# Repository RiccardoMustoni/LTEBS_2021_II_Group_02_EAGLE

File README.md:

# LTEBS_2021_II_Group_02_EAGLE

### Final Version 
The aim of the project is to design a PCB embedding the PSoC 5LP micro-controller in order to evaluate its performance and to determine if such uC is suitable for the project. The PCB embeds the CY8CKIT-059 kit, which will be soldered on male jumpers, and other additional components required to coduct the proper testing. 

The project consists in the design of a schematic, a board, and a library containing the necessary components. Design rules are added according to the technical specifications reported in the manufacturer website MDSrl.

### Project Folder 
The folder contains the schematic ("Group_02.sch") and the board ("Group_02.brd") used to create the final PCB.

### Library Folder 
The folder contains the library ("Group_02_Library.lbr") for the components TCA9546A and TMUX1208 with footprints, symbols and devices. 

### Design Rules Folder 
The folder contains the design rules ("Group_02.dru") according to the technical info on the manufacturer website. 

### Contributors 

Mancini Giorgia,
Mustoni Riccardo

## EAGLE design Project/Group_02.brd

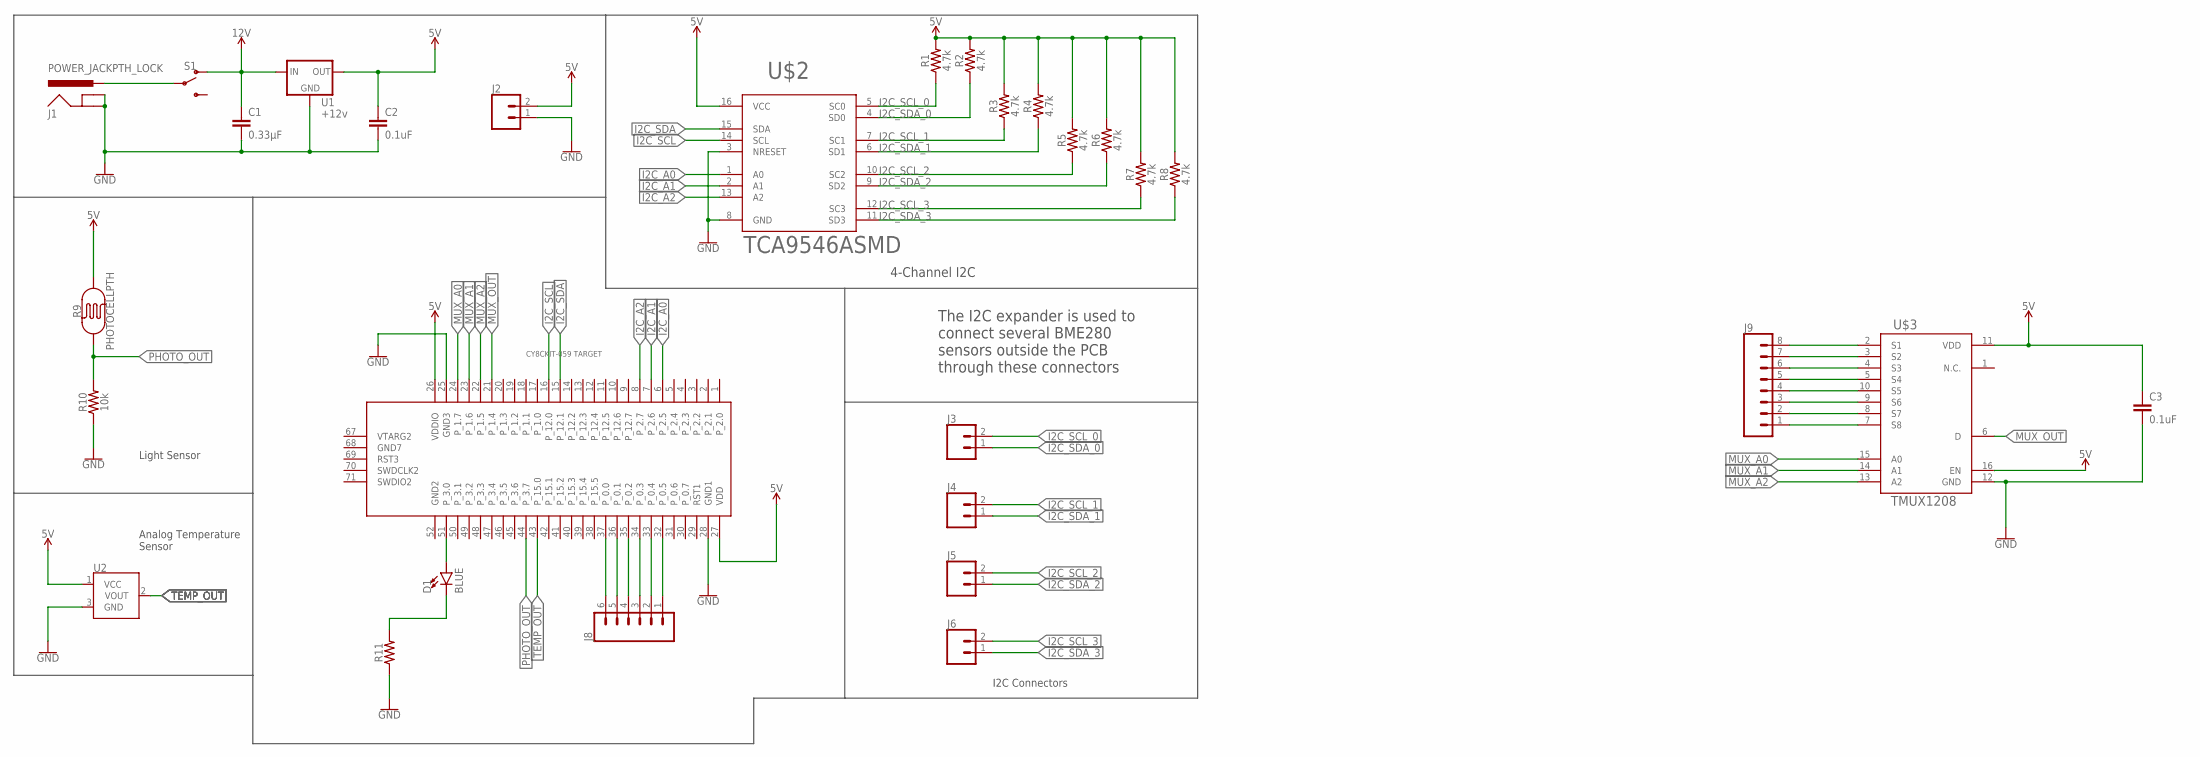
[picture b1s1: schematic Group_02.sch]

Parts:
C1: 0.33µF; 0805
C2, C3: 0.1uF; CAP-PTH-SMALL-KIT
D1: BLUE; LED-1206
J1: POWER_JACKPTH_LOCK; POWER_JACK_PTH_LOCK
J2, J3, J4, J5, J6: CONN_02; 1X02
J8: CONN_06LOCK; 1X06_LOCK
J9: CONN_08LOCK; 1X08_LOCK
R1, R2, R3, R4, R5, R6, R7, R8: 4.7k; 0603
R9: PHOTOCELLPTH; PHOTOCELL
R10: 10k; 0603
R11: AXIAL-0.3
S1: SWITCH-SPDT-PTH-11.6X4.0MM; SWITCH_SPDT_PTH_11.6X4.0MM
U1: +12v; TO-252
U2: TMP36GT9; TO-92
U$1: CY8CKIT-059_TARGET
U$2: TCA9546ASMD; TSSOP-16
U$3: TMUX1208; QFN-16

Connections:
5V: C2.1, C3.1, J2.2, R1.2, R2.2, R3.2, R4.2, R5.2, R6.2, R7.2, R8.2, R9.2, U1.2 (OUT), U2.1 (VCC), U$1.26 (VDDIO), U$1.27 (VDD), U$2.16 (VCC), U$3.11 (VDD), U$3.16 (EN)
12V: C1.1, S1.1 (O), U1.1 (IN)
GND: C1.2, C2.2, C3.2, J1.GND, J1.GNDBREAK, J2.1, R10.1, R11.P$1 (1), U1.3 (GND), U2.3 (GND), U$1.25 (GND3), U$1.28 (GND1), U$2.3 (NRESET), U$2.8 (GND), U$3.12 (GND)
I2C_A0: U$1.6 (P_2.5), U$2.1 (A0)
I2C_A1: U$1.7 (P_2.6), U$2.2 (A1)
I2C_A2: U$1.8 (P_2.7), U$2.13 (A2)
I2C_SCL: U$1.16 (P_12.0), U$2.14 (SCL)
I2C_SCL_0: J3.2, R1.1, U$2.5 (SC0)
I2C_SCL_1: J4.2, R3.1, U$2.7 (SC1)
I2C_SCL_2: J5.2, R5.1, U$2.10 (SC2)
I2C_SCL_3: J6.2, R7.1, U$2.12 (SC3)
I2C_SDA: U$1.15 (P_12.1), U$2.15 (SDA)
I2C_SDA_0: J3.1, R2.1, U$2.4 (SD0)
I2C_SDA_1: J4.1, R4.1, U$2.6 (SD1)
I2C_SDA_2: J5.1, R6.1, U$2.9 (SD2)
I2C_SDA_3: J6.1, R8.1, U$2.11 (SD3)
MUX_A0: U$1.24 (P_1.7), U$3.15 (A0)
MUX_A1: U$1.23 (P_1.6), U$3.14 (A1)
MUX_A2: U$1.22 (P_1.5), U$3.13 (A2)
MUX_OUT: U$1.21 (P_1.4), U$3.6 (D)
unnamed: J1.PWR, S1.2
unnamed: J8.1, U$1.32 (P_0.5)
unnamed: J8.2, U$1.33 (P_0.4)
unnamed: J8.3, U$1.34 (P_0.3)
unnamed: J8.4, U$1.35 (P_0.2)
unnamed: J8.5, U$1.36 (P_0.1)
unnamed: J8.6, U$1.37 (P_0.0)
unnamed: D1.A, U$1.51 (P_3.0)
unnamed: D1.C, R11.P$2 (2)
unnamed: J9.8, U$3.2 (S1)
unnamed: J9.7, U$3.3 (S2)
unnamed: J9.6, U$3.4 (S3)
unnamed: J9.5, U$3.5 (S4)
unnamed: J9.4, U$3.10 (S5)
unnamed: J9.3, U$3.9 (S6)
unnamed: J9.2, U$3.8 (S7)
unnamed: J9.1, U$3.7 (S8)
PHOTO_OUT: R9.1, R10.2, U$1.44 (P_3.7)
TEMP_OUT: U2.2 (VOUT), U$1.43 (P_15.0)

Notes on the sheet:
Light Sensor
Analog Temperature Sensor
I2C Connectors
The I2C expander is used to connect several BME280 sensors outside the PCB through these connectors
4-Channel I2C

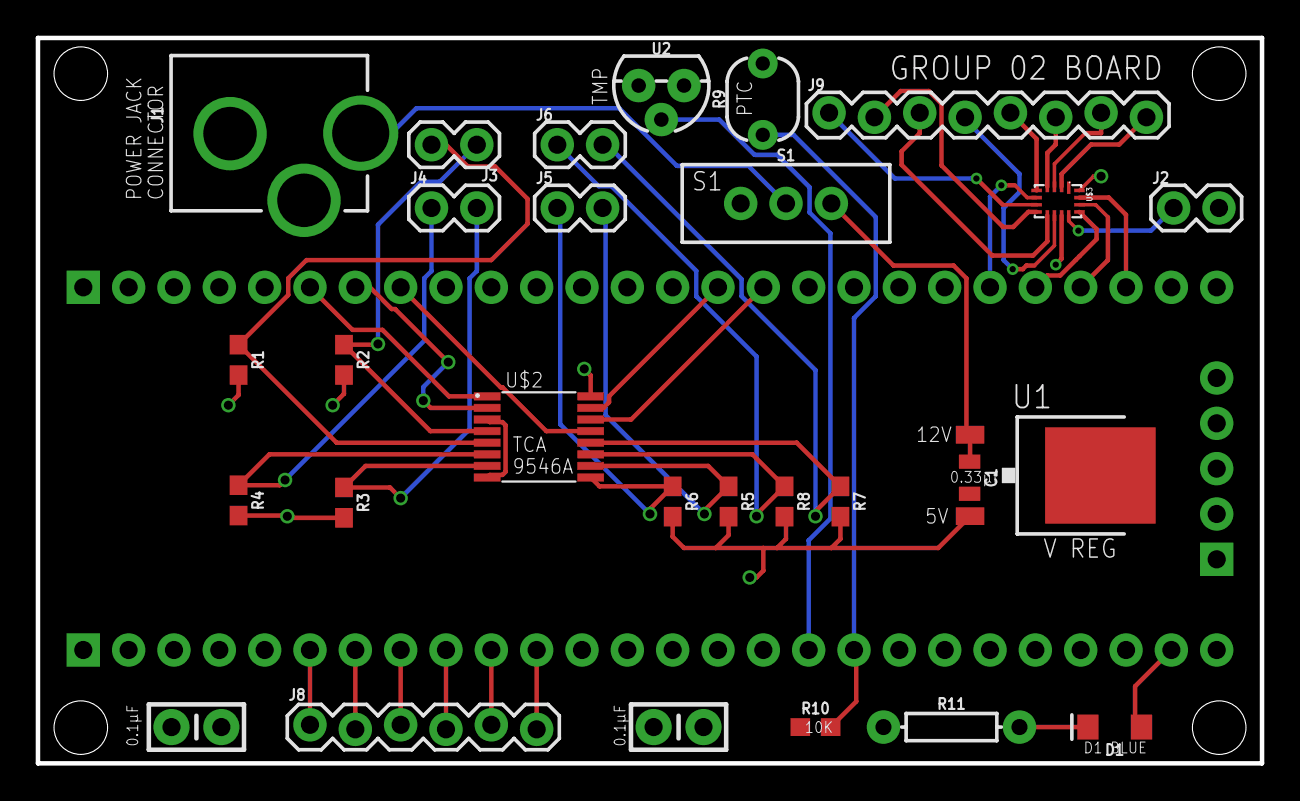
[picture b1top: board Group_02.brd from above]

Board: 2 copper layers, 68.6 x 40.6 mm, 29 parts (1 on the bottom side), 39 nets.

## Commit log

2021-03-18 Creation of library
2021-03-18 Libreria completa
2021-03-18 Mux schematico centrato
2021-03-18 Piccolo aggiustamento dimensioni mux
2021-03-19 Inizio Schematico
2021-03-19 Aggiornamento symbols TMUX
2021-03-19 Aggiornamento schematico
2021-03-19 Aggiornamento symbol tca
2021-03-19 Completamento schematico con tca
2021-03-19 Creato albero directories
2021-03-20 Ora è completo
2021-03-20 PCB completa
2021-03-21 Creazione desgin rules
2021-03-21 Posizionamento holes
2021-03-21 Aggiornamento libreria
2021-03-21 Aggiornamento M3 holes
2021-03-21 Aggiunto .gitignore
2021-03-21 Identification badge
2021-03-21 Routing width 10 mils
2021-03-21 Ancora wire width 10 mils
2021-03-21 Pulizia cavi
2021-03-22 Tutti i cavi a 10 mils
2021-03-22 Correzione design rules ed errori in board
2021-03-22 Aggiornamento dimensioni board
2021-03-22 Aggiustati design rules e misure guide board, no errori
2021-03-22 Aggiornamento diametro holes
2021-03-22 Completamento collegamenti schematico
2021-03-22 Correzioni tracce board
2021-03-22 Completamento board
2021-03-22 Tolto slave1 badge
2021-03-22 Modifica a gitignore
2021-03-23 Ottimizzazione dimensioni board
2021-03-23 Completamento board super ridotta
2021-03-23 Progetto board super ridotta
2021-03-24 Piccole modifiche e spostamenti
2021-03-24 Piccola modifica gitignore
2021-03-24 File completi
2021-03-24 Aggiustamento posizionamento pin
2021-03-24 Aggiornamento dimensioni
2021-03-25 Aggiunta isolamento
2021-03-25 Isolamento bottom layer
2021-03-26 aggiornamento design rules
2021-03-26 rotazione power jack
2021-03-26 file finali
2021-03-26 Final Version

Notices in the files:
parts and their libraries:
SparkFun-Aesthetics: Licensing: Creative Commons ShareAlike 4.0 International - https://creativecommons.org/licenses/by-sa/4.0
